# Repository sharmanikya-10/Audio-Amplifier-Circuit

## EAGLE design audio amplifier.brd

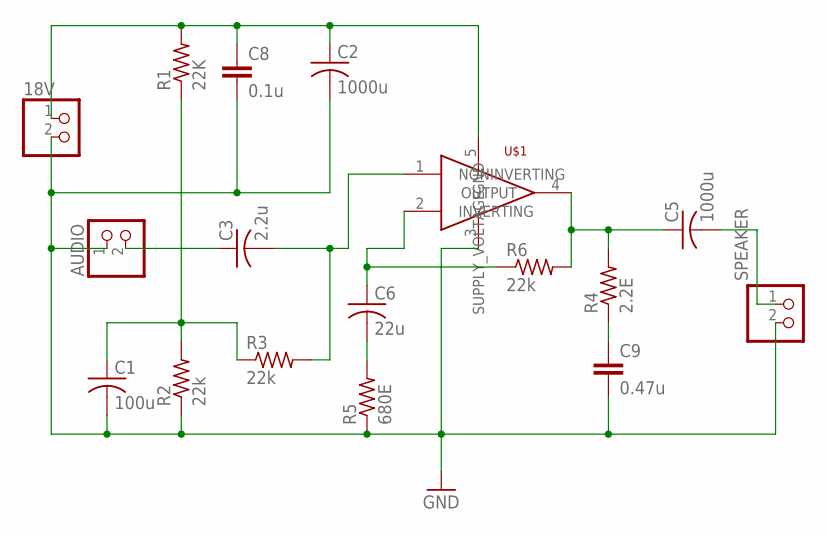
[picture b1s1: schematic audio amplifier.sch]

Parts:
18V: PINHD-1X2; 1X02
AUDIO: PINHD-1X2; 1X02
C1: 100u; C025-024X044
C2, C5: 1000u; C025-024X044
C3: 2.2u; C025-024X044
C6: 22u; C025-024X044
C8: 0.1u; C025-025X050
C9: 0.47u; C025-025X050
R1: 22K; 0204/7
R2, R3, R6: 22k; 0204/7
R4: 2.2E; 0204/7
R5: 680E; 0204/7
SPEAKER: PINHD-1X2; 1X02
U$1: TDA2050; PENTAWATT

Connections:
GND: 18V.2, AUDIO.1, C1.2, C2.2, C8.2, C9.2, R2.1, R5.1, SPEAKER.2, U$1.3 (GND)
unnamed: 18V.1, C2.1, C8.1, R1.2, U$1.5 (SUPPLY_VOLTAGE)
unnamed: AUDIO.2, C3.1
unnamed: C3.2, R3.2, U$1.1 (NONINVERTING)
unnamed: C6.2, R5.2
unnamed: C6.1, R6.1, U$1.2 (INVERTING)
unnamed: C1.1, R1.1, R2.2, R3.1
unnamed: C9.1, R4.1
unnamed: C5.1, R4.2, R6.2, U$1.4 (OUTPUT)
unnamed: C5.2, SPEAKER.1

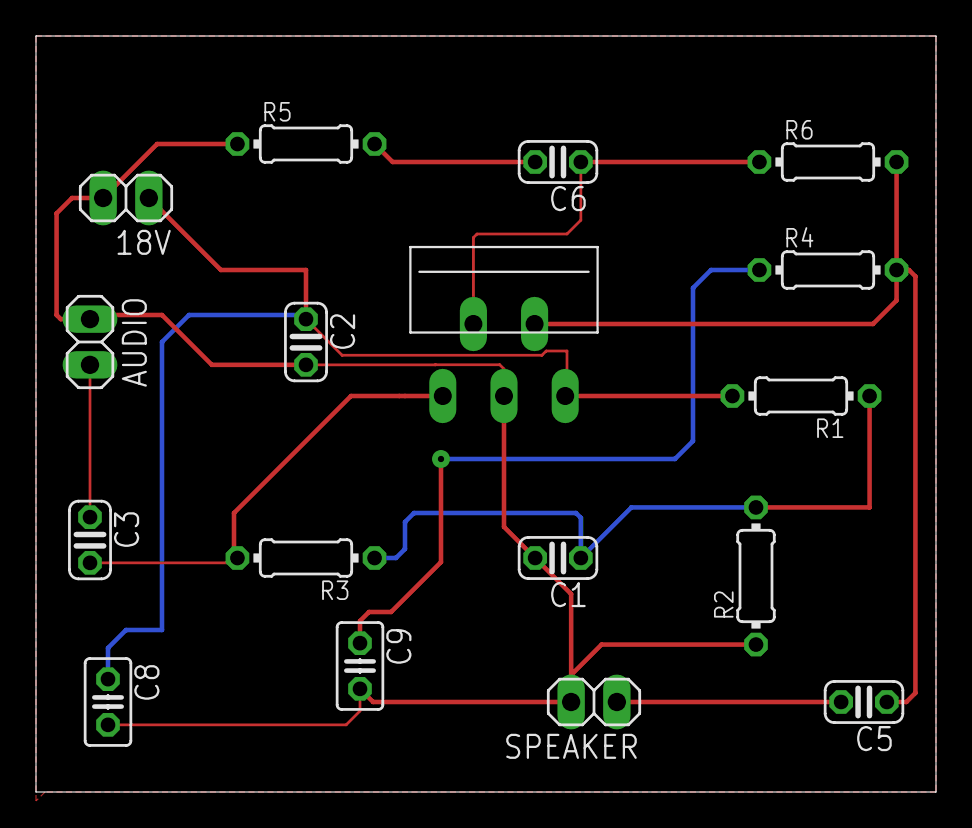
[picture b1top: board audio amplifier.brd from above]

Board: 2 copper layers, 50.0 x 42.0 mm, 17 parts (0 on the bottom side), 10 nets.

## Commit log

2022-09-08 Added Files
